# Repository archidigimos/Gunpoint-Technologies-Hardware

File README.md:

# Gunpoint-Technologies-Hardware
Lasertag gaming hardware. Product developed for gaming, entertainment and battlefield simulation purpose for military.

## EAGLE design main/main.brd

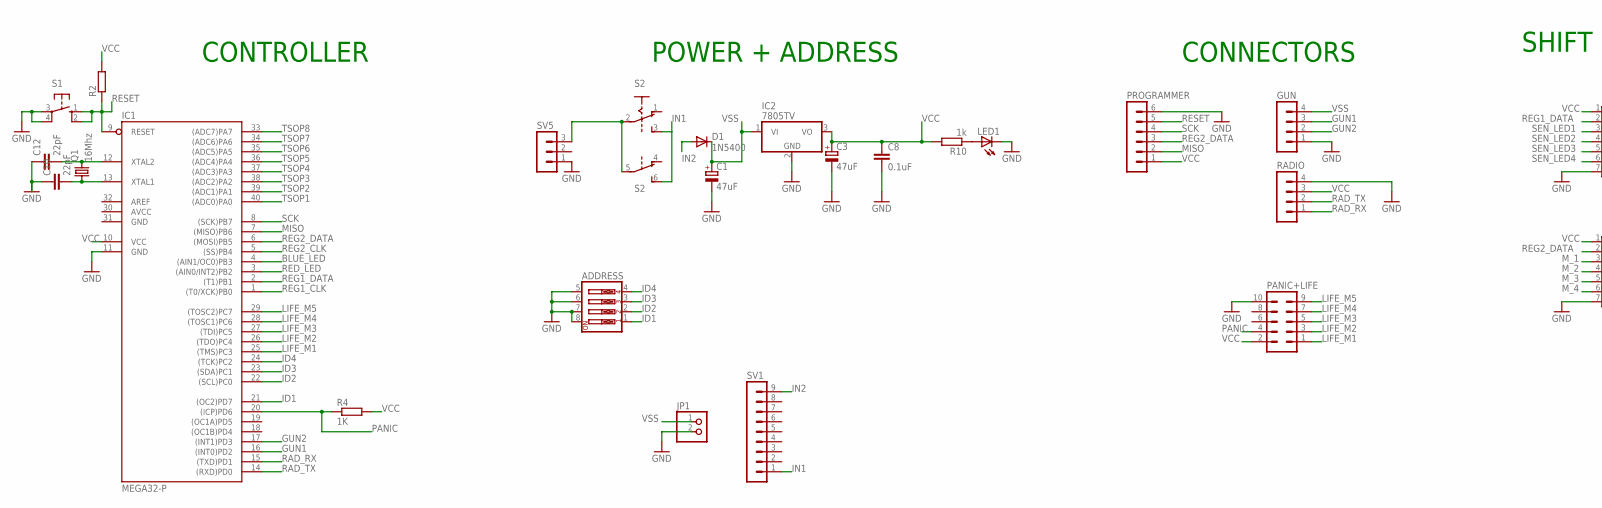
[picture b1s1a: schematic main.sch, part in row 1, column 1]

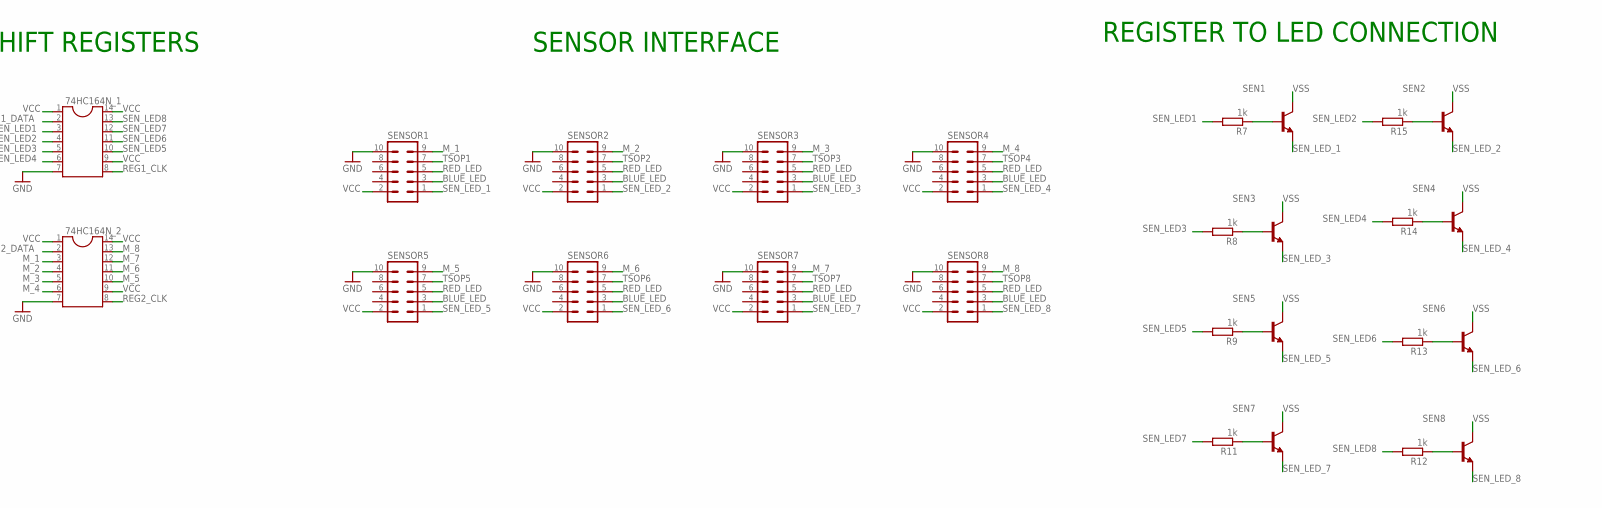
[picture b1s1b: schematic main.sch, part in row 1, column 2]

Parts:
74HC164N_1, 74HC164N_2: DIL14
ADDRESS: SW_DIP-4; EDG-04
C1, C3: 47uF; E2,5-6
C8: 0.1uF; C025-025X050
C10, C12: 22pF; C025-025X050
D1: 1N5400; DO201-15
GUN: MA04-1
IC1: MEGA32-P; DIL40
IC2: 7805TV; TO220V
JP1: PINHD-1X2; 1X02
LED1: LED5MM
PANIC+LIFE: ML10
PROGRAMMER: MA06-1
Q1: 16Mhz; HC49U70
R2: R-EU_0207/10; 0207/10
R4: 1K; 0207/10
R7, R8, R9, R10, R11, R12, R13, R14, R15: 1k; 0207/10
RADIO: MA04-1
S1: 10-XX; B3F-10XX
S2: A68-A31
SEN1, SEN2, SEN3, SEN4, SEN5, SEN6, SEN7, SEN8: BC547; TO92
SENSOR1, SENSOR2, SENSOR3, SENSOR4, SENSOR5, SENSOR6, SENSOR7, SENSOR8: ML10
SV1: MA09-1
SV5: MA03-1

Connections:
AVCC: IC1.30 (AVCC)
BLUE_LED: IC1.4 ((AIN1/OC0)PB3), SENSOR1.3, SENSOR2.3, SENSOR3.3, SENSOR4.3, SENSOR5.3, SENSOR6.3, SENSOR7.3, SENSOR8.3
GND: 74HC164N_1.7, 74HC164N_2.7, ADDRESS.5, ADDRESS.6, ADDRESS.7, ADDRESS.8, C1.-, C3.-, C8.2, C10.1, C12.1, GUN.1, IC1.11 (GND), IC1.31 (GND), IC2.2 (GND), JP1.2, LED1.K (C), PANIC+LIFE.10, PROGRAMMER.6, RADIO.4, S1.3, S1.4 (P1), SENSOR1.10, SENSOR2.10, SENSOR3.10, SENSOR4.10, SENSOR5.10, SENSOR6.10, SENSOR7.10, SENSOR8.10, SV5.1
GUN1: GUN.3, IC1.16 ((INT0)PD2)
GUN2: GUN.2, IC1.17 ((INT1)PD3)
ID1: ADDRESS.1, IC1.21 ((OC2)PD7)
ID2: ADDRESS.2, IC1.22 ((SCL)PC0)
ID3: ADDRESS.3, IC1.23 ((SDA)PC1)
ID4: ADDRESS.4, IC1.24 ((TCK)PC2)
IN1: S2.3 (S), S2.6 (S), SV1.1
IN2: D1.A, SV1.9
LIFE_M1: IC1.25 ((TMS)PC3), PANIC+LIFE.1
LIFE_M2: IC1.26 ((TDO)PC4), PANIC+LIFE.3
LIFE_M3: IC1.27 ((TDI)PC5), PANIC+LIFE.5
LIFE_M4: IC1.28 ((TOSC1)PC6), PANIC+LIFE.7
LIFE_M5: IC1.29 ((TOSC2)PC7), PANIC+LIFE.9
MISO: IC1.7 ((MISO)PB6), PROGRAMMER.2
M_1: 74HC164N_2.3, SENSOR1.9
M_2: 74HC164N_2.4, SENSOR2.9
M_3: 74HC164N_2.5, SENSOR3.9
M_4: 74HC164N_2.6, SENSOR4.9
M_5: 74HC164N_2.10, SENSOR5.9
M_6: 74HC164N_2.11, SENSOR6.9
M_7: 74HC164N_2.12, SENSOR7.9
M_8: 74HC164N_2.13, SENSOR8.9
unnamed: C12.2, IC1.12 (XTAL2), Q1.2
unnamed: C10.2, IC1.13 (XTAL1), Q1.1
unnamed: LED1.A, R10.1
unnamed: R7.1, SEN1.2 (B)
unnamed: R15.1, SEN2.2 (B)
unnamed: S2.2, S2.5, SV5.3
unnamed: R8.1, SEN3.2 (B)
unnamed: R14.1, SEN4.2 (B)
unnamed: R9.1, SEN5.2 (B)
unnamed: R13.1, SEN6.2 (B)
unnamed: R11.1, SEN7.2 (B)
unnamed: R12.1, SEN8.2 (B)
PANIC: IC1.20 ((ICP)PD6), PANIC+LIFE.4, R4.1
RAD_RX: IC1.15 ((TXD)PD1), RADIO.1
RAD_TX: IC1.14 ((RXD)PD0), RADIO.2
RED_LED: IC1.3 ((AIN0/INT2)PB2), SENSOR1.5, SENSOR2.5, SENSOR3.5, SENSOR4.5, SENSOR5.5, SENSOR6.5, SENSOR7.5, SENSOR8.5
REG1_CLK: 74HC164N_1.8, IC1.1 ((T0/XCK)PB0)
REG1_DATA: 74HC164N_1.2, IC1.2 ((T1)PB1)
REG2_CLK: 74HC164N_2.8, IC1.5 ((SS)PB4)
REG2_DATA: 74HC164N_2.2, IC1.6 ((MOSI)PB5), PROGRAMMER.3
RESET: IC1.9 (RESET), PROGRAMMER.5, R2.1, S1.1 (S), S1.2 (S1)
SCK: IC1.8 ((SCK)PB7), PROGRAMMER.4
SEN_LED1: 74HC164N_1.3, R7.2
SEN_LED2: 74HC164N_1.4, R15.2
SEN_LED3: 74HC164N_1.5, R8.2
SEN_LED4: 74HC164N_1.6, R14.2
SEN_LED5: 74HC164N_1.10, R9.2
SEN_LED6: 74HC164N_1.11, R13.2
SEN_LED7: 74HC164N_1.12, R11.2
SEN_LED8: 74HC164N_1.13, R12.2
SEN_LED_1: SEN1.1 (E), SENSOR1.1
SEN_LED_2: SEN2.1 (E), SENSOR2.1
SEN_LED_3: SEN3.1 (E), SENSOR3.1
SEN_LED_4: SEN4.1 (E), SENSOR4.1
SEN_LED_5: SEN5.1 (E), SENSOR5.1
SEN_LED_6: SEN6.1 (E), SENSOR6.1
SEN_LED_7: SEN7.1 (E), SENSOR7.1
SEN_LED_8: SEN8.1 (E), SENSOR8.1
TSOP1: IC1.40 ((ADC0)PA0), SENSOR1.7
TSOP2: IC1.39 ((ADC1)PA1), SENSOR2.7
TSOP3: IC1.38 ((ADC2)PA2), SENSOR3.7
TSOP4: IC1.37 ((ADC3)PA3), SENSOR4.7
TSOP5: IC1.36 ((ADC4)PA4), SENSOR5.7
TSOP6: IC1.35 ((ADC5)PA5), SENSOR6.7
TSOP7: IC1.34 ((ADC6)PA6), SENSOR7.7
TSOP8: IC1.33 ((ADC7)PA7), SENSOR8.7
VCC: 74HC164N_1.1, 74HC164N_1.9, 74HC164N_1.14, 74HC164N_2.1, 74HC164N_2.9, 74HC164N_2.14, C3.+, C8.1, IC1.10 (VCC), IC2.3 (VO), PANIC+LIFE.2, PROGRAMMER.1, R2.2, R4.2, R10.2, RADIO.3, SENSOR1.2, SENSOR2.2, SENSOR3.2, SENSOR4.2, SENSOR5.2, SENSOR6.2, SENSOR7.2, SENSOR8.2
VSS: C1.+, D1.C, GUN.4, IC2.1 (VI), JP1.1, SEN1.3 (C), SEN2.3 (C), SEN3.3 (C), SEN4.3 (C), SEN5.3 (C), SEN6.3 (C), SEN7.3 (C), SEN8.3 (C)

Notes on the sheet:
CONTROLLER
POWER + ADDRESS
CONNECTORS
SHIFT REGISTERS
SENSOR INTERFACE
REGISTER TO LED CONNECTION

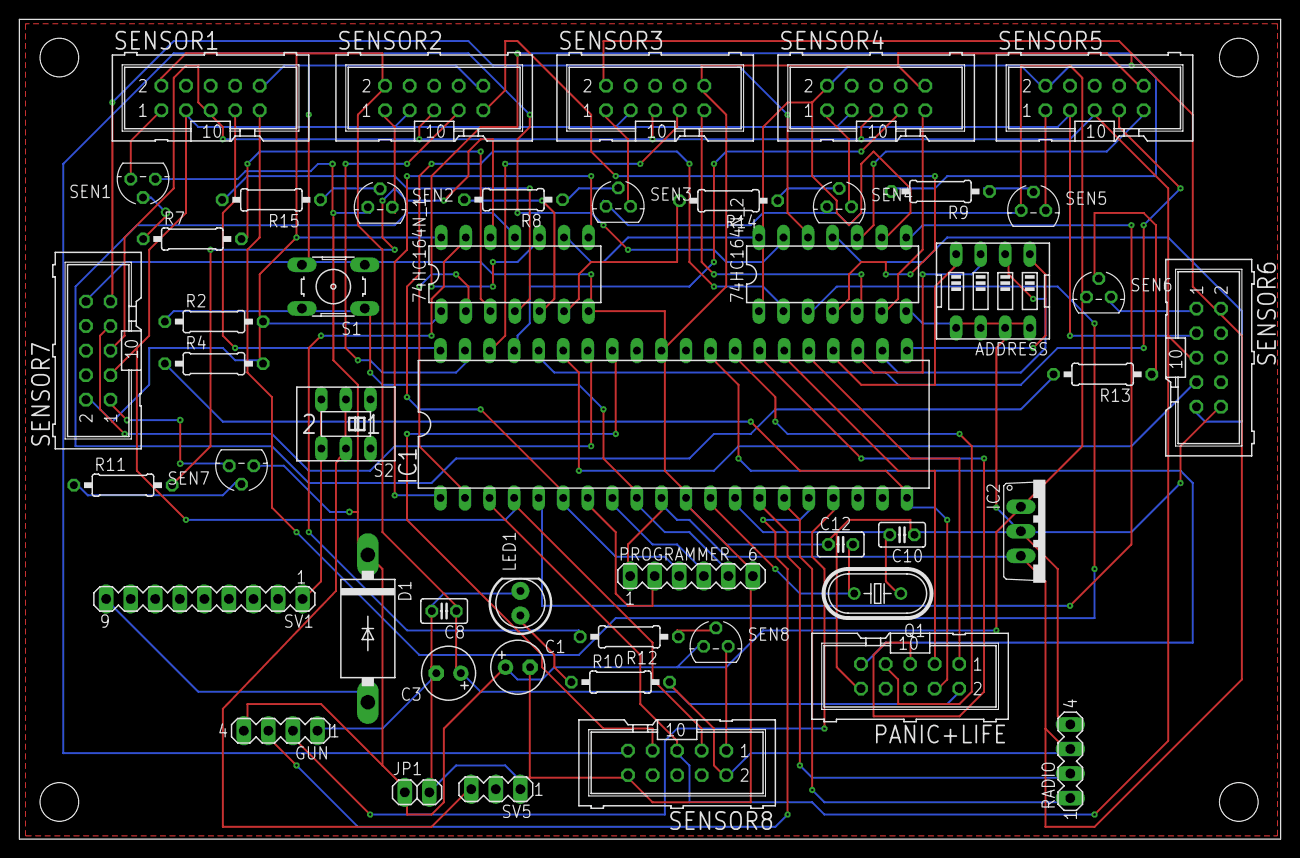
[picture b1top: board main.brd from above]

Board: 2 copper layers, 130.5 x 84.8 mm, 49 parts (0 on the bottom side), 72 nets.

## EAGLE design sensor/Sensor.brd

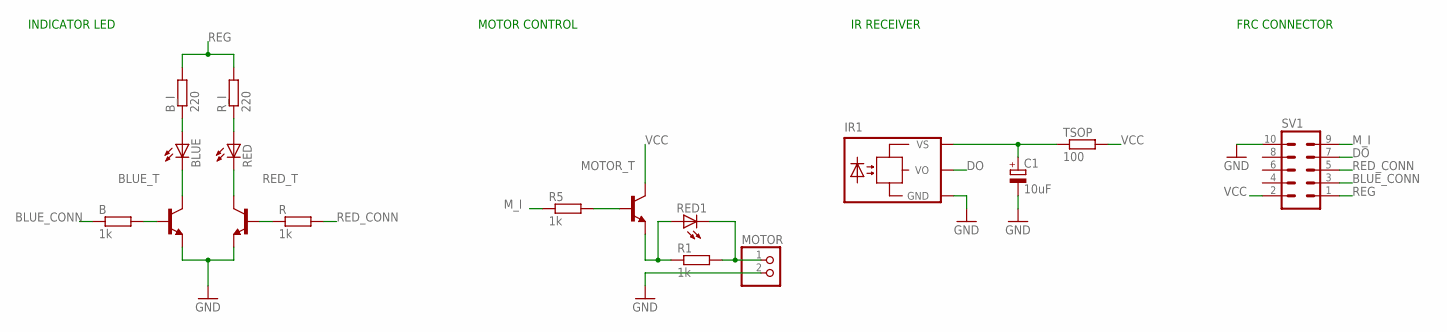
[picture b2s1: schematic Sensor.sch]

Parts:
B: 1k; 0207/12
BLUE: LED5MM
BLUE_T: BC547; TO92
B_I: 220; 0207/12
C1: 10uF; E2,5-6
IR1: TSOP1730TB1; TSOP17_TB1
MOTOR: PINHD-1X2; 1X02
MOTOR_T: BC547; TO92
R, R1, R5: 1k; 0207/12
RED: LED5MM
RED1: LEDSMT1206; 1206
RED_T: BC547; TO92
R_I: 220; 0207/12
SV1: ML10
TSOP: 100; 0207/12

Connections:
BLUE_CONN: B.1, SV1.3
DO: IR1.VO, SV1.7
GND: BLUE_T.1 (E), C1.-, IR1.GND, MOTOR.2, RED_T.1 (E), SV1.10
M_I: R5.1, SV1.9
unnamed: BLUE.A, B_I.1
unnamed: C1.+, IR1.VS, TSOP.1
unnamed: BLUE.K (C), BLUE_T.3 (C)
unnamed: RED.K (C), RED_T.3 (C)
unnamed: MOTOR_T.2 (B), R5.2
unnamed: MOTOR_T.1 (E), R1.1, RED1.A
unnamed: B.2, BLUE_T.2 (B)
unnamed: R.1, RED_T.2 (B)
unnamed: MOTOR.1, R1.2, RED1.C
RED_CONN: R.2, SV1.5
REG: B_I.2, R_I.2, SV1.1
R_I: RED.A, R_I.1
VCC: MOTOR_T.3 (C), SV1.2, TSOP.2

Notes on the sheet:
INDICATOR LED
MOTOR CONTROL
IR RECEIVER
FRC CONNECTOR

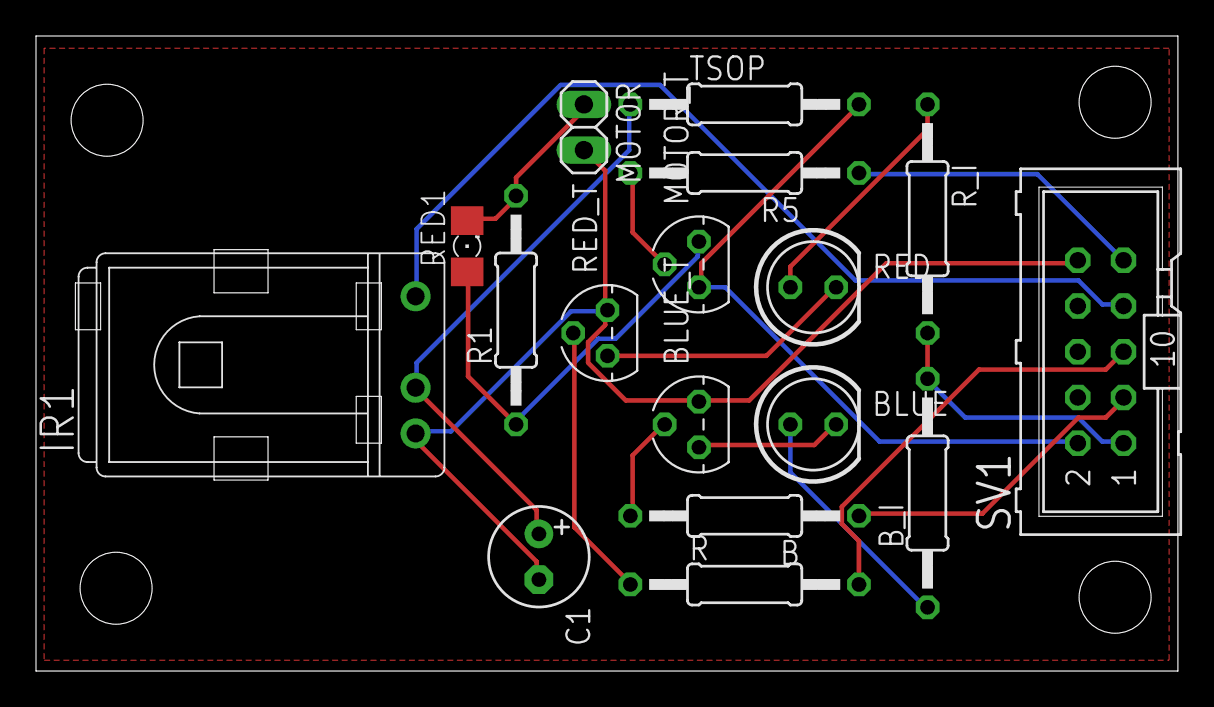
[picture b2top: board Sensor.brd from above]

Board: 2 copper layers, 63.4 x 35.3 mm, 17 parts (0 on the bottom side), 17 nets.

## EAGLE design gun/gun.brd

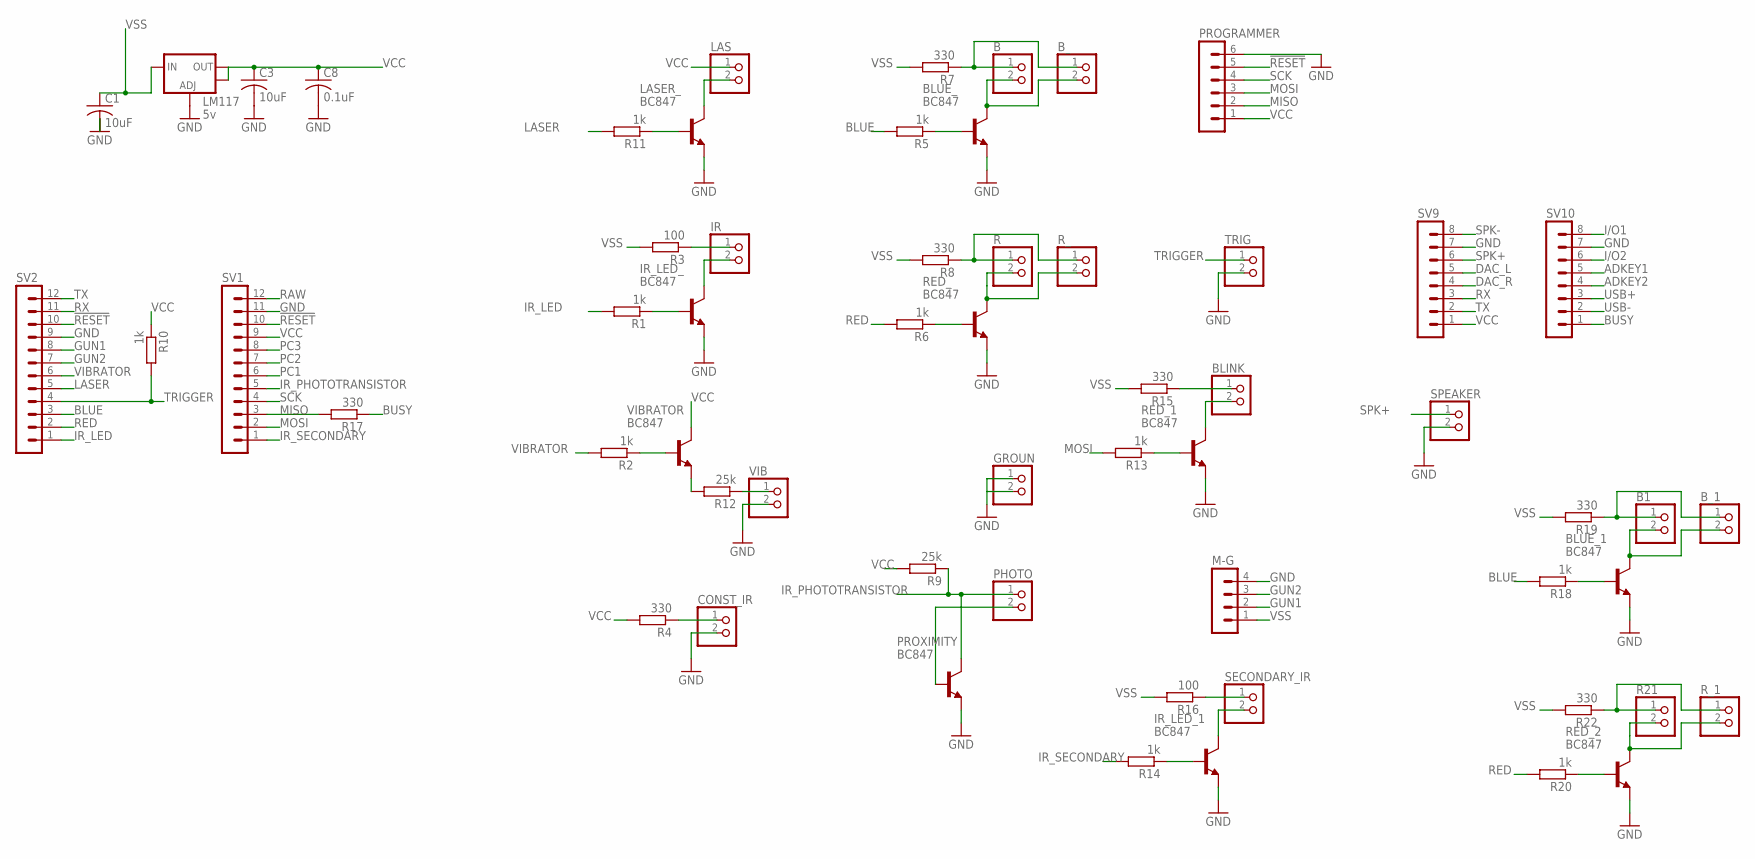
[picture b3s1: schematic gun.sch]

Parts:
B, B1: PINHD-1X2; 1X02
BLINK: PINHD-1X2; 1X02
BLUE_, BLUE_1: BC847; SOT23
B_, B_1: PINHD-1X2; 1X02
C1, C3: 10uF; C0805
C8: 0.1uF; C0805
CONST_IR: PINHD-1X2; 1X02
GROUN: PINHD-1X2; 1X02
IR: PINHD-1X2; 1X02
IR_LED_, IR_LED_1: BC847; SOT23
LAS: PINHD-1X2; 1X02
LASER_: BC847; SOT23
LM117: 5v; SOT223
M-G: MA04-1
PHOTO: PINHD-1X2; 1X02
PROGRAMMER: MA06-1
PROXIMITY: BC847; SOT23
R, R21: PINHD-1X2; 1X02
R1, R2, R5, R6, R10, R11, R13, R14, R18, R20: 1k; M1206
R3, R16: 100; M1206
R4, R7, R8, R15, R17, R19, R22: 330; M1206
R9, R12: 25k; M1206
RED_, RED_1, RED_2: BC847; SOT23
R_, R_1: PINHD-1X2; 1X02
SECONDARY_IR: PINHD-1X2; 1X02
SPEAKER: PINHD-1X2; 1X02
SV1, SV2: MA12-1
SV9, SV10: MA08-1
TRIG: PINHD-1X2; 1X02
VIB: PINHD-1X2; 1X02
VIBRATOR: BC847; SOT23

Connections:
!RESET: PROGRAMMER.5, SV1.10, SV2.10
ADKEY1: SV10.5
ADKEY2: SV10.4
BLUE: R5.2, R18.2, SV2.3
BUSY: R17.1, SV10.1
DAC_L: SV9.5
DAC_R: SV9.4
GND: BLUE_.2 (E), BLUE_1.2 (E), C1.2, C3.2, C8.2, CONST_IR.2, GROUN.1, GROUN.2, IR_LED_.2 (E), IR_LED_1.2 (E), LASER_.2 (E), LM117.1 (ADJ), M-G.4, PROGRAMMER.6, PROXIMITY.2 (E), RED_.2 (E), RED_1.2 (E), RED_2.2 (E), SPEAKER.2, SV1.11, SV2.9, SV9.7, SV10.7, TRIG.2, VIB.2
GUN1: M-G.2, SV2.8
GUN2: M-G.3, SV2.7
I/O1: SV10.8
I/O2: SV10.6
IR_LED: R1.2, SV2.1
IR_PHOTOTRANSISTOR: PHOTO.1, PROXIMITY.3 (C), R9.1, SV1.5
IR_SECONDARY: R14.2, SV1.1
LASER: R11.2, SV2.5
MISO: PROGRAMMER.2, R17.2, SV1.3
MOSI: PROGRAMMER.3, R13.2, SV1.2
unnamed: PHOTO.2, PROXIMITY.1 (B)
unnamed: R12.1, VIB.1
unnamed: IR_LED_.1 (B), R1.1
unnamed: R2.1, VIBRATOR.1 (B)
unnamed: R12.2, VIBRATOR.2 (E)
unnamed: IR.1, R3.1
unnamed: IR.2, IR_LED_.3 (C)
unnamed: CONST_IR.1, R4.1
unnamed: LAS.2, LASER_.3 (C)
unnamed: R13.1, RED_1.1 (B)
unnamed: BLUE_.1 (B), R5.1
unnamed: B.2, BLUE_.3 (C), B_.2
unnamed: R6.1, RED_.1 (B)
unnamed: R.2, RED_.3 (C), R_.2
unnamed: B.1, B_.1, R7.1
unnamed: R.1, R8.1, R_.1
unnamed: BLINK.2, RED_1.3 (C)
unnamed: BLINK.1, R15.1
unnamed: LASER_.1 (B), R11.1
unnamed: IR_LED_1.1 (B), R14.1
unnamed: IR_LED_1.3 (C), SECONDARY_IR.2
unnamed: R16.1, SECONDARY_IR.1
unnamed: BLUE_1.1 (B), R18.1
unnamed: B1.2, BLUE_1.3 (C), B_1.2
unnamed: B1.1, B_1.1, R19.1
unnamed: R20.1, RED_2.1 (B)
unnamed: R21.2, RED_2.3 (C), R_1.2
unnamed: R21.1, R22.1, R_1.1
PC1: SV1.6
PC2: SV1.7
PC3: SV1.8
RAW: SV1.12
RED: R6.2, R20.2, SV2.2
RX: SV2.11, SV9.3
SCK: PROGRAMMER.4, SV1.4
SPK+: SPEAKER.1, SV9.6
SPK-: SV9.8
TRIGGER: R10.2, SV2.4, TRIG.1
TX: SV2.12, SV9.2
USB+: SV10.3
USB-: SV10.2
VCC: C3.1, C8.1, LAS.1, LM117.2 (OUT), LM117.4 (OUT), PROGRAMMER.1, R4.2, R9.2, R10.1, SV1.9, SV9.1, VIBRATOR.3 (C)
VIBRATOR: R2.2, SV2.6
VSS: C1.1, LM117.3 (IN), M-G.1, R3.2, R7.2, R8.2, R15.2, R16.2, R19.2, R22.2

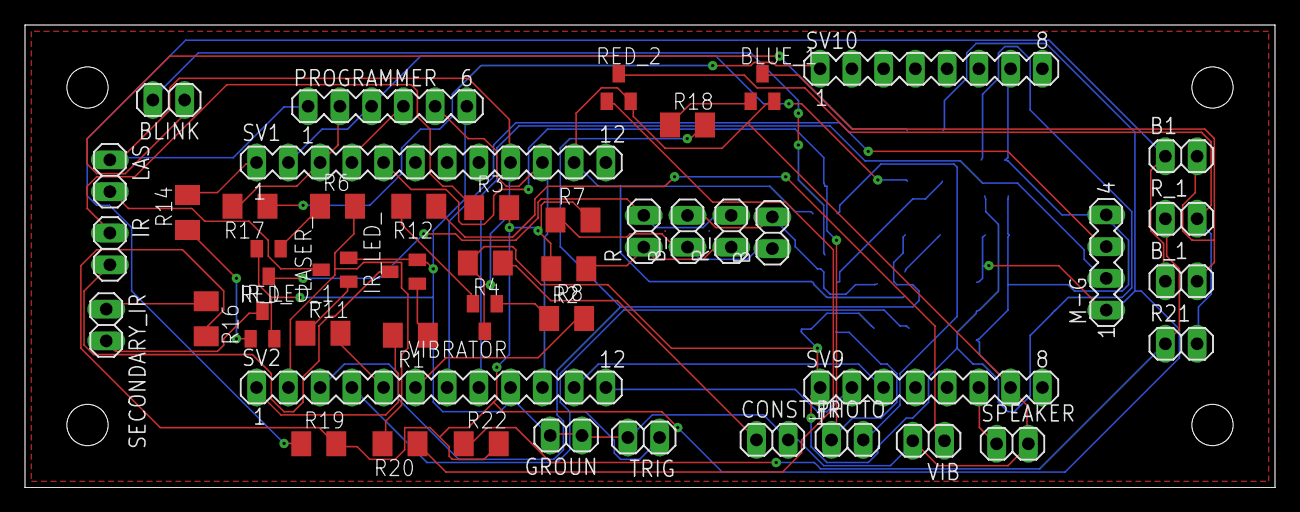
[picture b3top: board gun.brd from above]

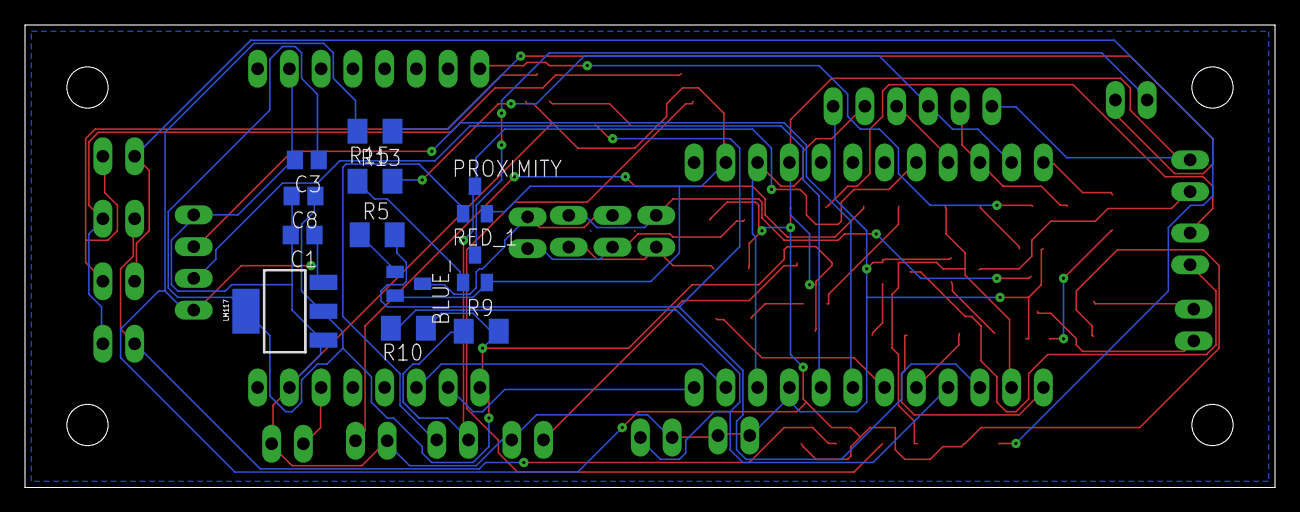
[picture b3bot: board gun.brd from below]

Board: 2 copper layers, 100.0 x 37.0 mm, 59 parts (12 on the bottom side), 49 nets.

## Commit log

2017-08-08 :confetti_ball: Added .gitattributes & .gitignore files
2017-08-08 Screenshot
